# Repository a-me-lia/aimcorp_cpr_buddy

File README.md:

# Production Instructions

The files in the `/production` folder are ready for ordering at JLCPCB or most other PCB brokering services.

- **Board Design**: This board is designed as a 2-layer PCB. The quoting software should automatically select the minimum tolerances needed.
- **BOM Handling**: 
    - After uploading the BOM, if a component did not autopopulate, locate the corresponding designator in the BOM file.
    - Use the LCSC part number from the BOM to search in the JLC Parts library for an identical component.
    - LCSC "C-numbers" can be directly used in JLCPCB for part selection.

# Programming Instructions

This board is compatible with a standard 6-pin FTDI breakout for programming.

- **Programming Port**: The programming port is not populated with a pin header, allowing direct insertion of the FTDI board.
- **Bootloader Mode Strapping**: Refer to the [ESP-12F datasheet](https://www.espressif.com/sites/default/files/documentation/0a-esp8266ex_datasheet_en.pdf) for details on bootloader mode strapping.
    - All physical interfaces for pin strapping are accessible via a 4-pin interface on the board.

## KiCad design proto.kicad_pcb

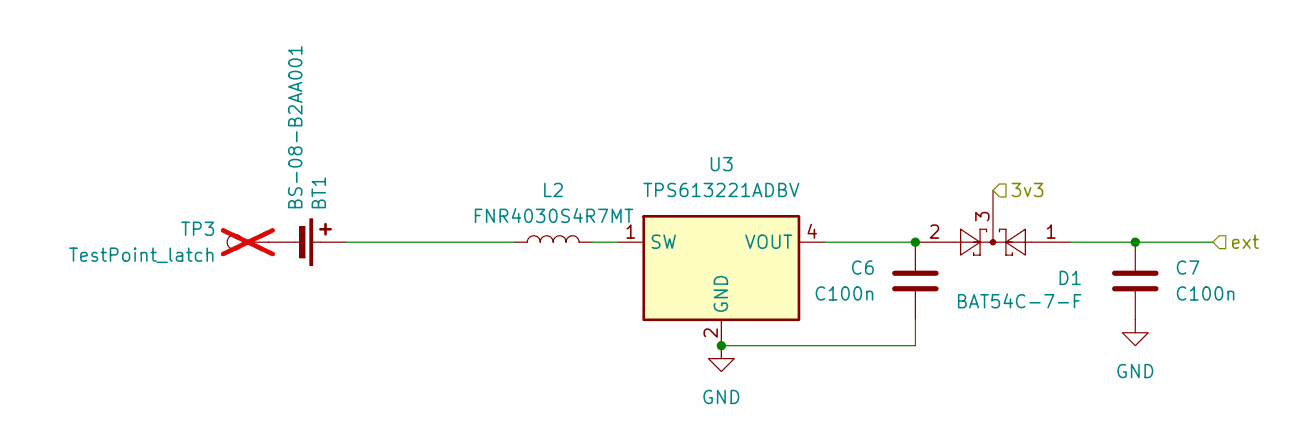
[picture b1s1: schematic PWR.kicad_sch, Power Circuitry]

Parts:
BT1: BS-08-B2AA001; LCSC C964777
C6, C7: C100n; C_0402_1005Metric; LCSC C60474
D1: BAT54C-7-F; SOT-23; LCSC C556168
L2: FNR4030S4R7MT; L_Changjiang_FNR4030S; LCSC C167874
TP3: TestPoint_latch; TestPoint_Bridge_Pitch2.0mm_Drill0.7mm; not fitted
U3: TPS613221ADBV; SOT-23-5; LCSC C2071121

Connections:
/DIFFAMP/3v3: D1.3; also elsewhere on the board
/ESP/ext: C7.1, D1.1; also elsewhere on the board
GND: C6.2, C7.2, U3.2 (GND); also elsewhere on the board
unnamed: BT1.+, L2.1
unnamed: BT1.-, TP3.1
unnamed: L2.2, U3.1 (SW)
unnamed: C6.1, D1.2, U3.4 (VOUT)

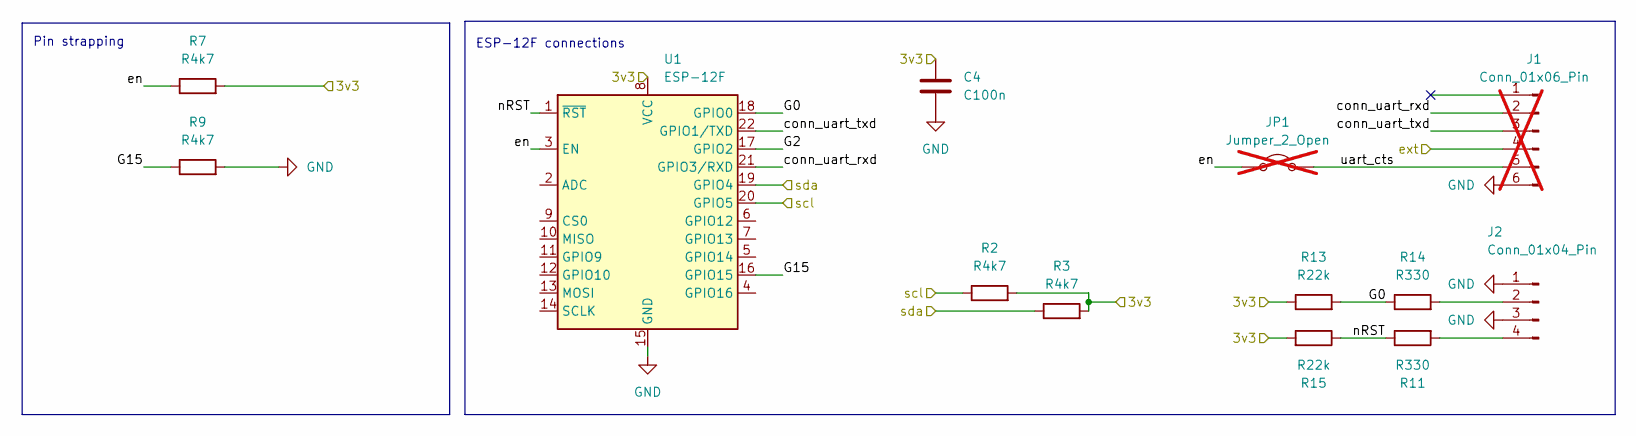
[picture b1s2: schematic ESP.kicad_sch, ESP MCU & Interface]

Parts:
C4: C100n; C_0402_1005Metric; LCSC C60474
J1: Conn_01x06_Pin; PinHeader_1x06_P2.54mm_Vertical; not fitted
J2: Conn_01x04_Pin; PinHeader_1x04_P2.54mm_Vertical; LCSC C6332197
JP1: Jumper_2_Open; SolderJumper-2_P1.3mm_Open_TrianglePad1.0x1.5mm; not fitted
R2, R3, R7, R9: R4k7; R_0402_1005Metric; LCSC C25940
R11, R14: R330; R_0402_1005Metric; LCSC C25104
R13, R15: R22k; R_0402_1005Metric; LCSC C82868
U1: ESP-12F; ESP-12E; LCSC C82891

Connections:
/DIFFAMP/3v3: C4.1, R2.2, R3.2, R7.2, R13.1, R15.2, U1.8 (VCC); also elsewhere on the board
/DIFFAMP/scl: R2.1, U1.20 (GPIO5); also elsewhere on the board
/DIFFAMP/sda: R3.1, U1.19 (GPIO4); also elsewhere on the board
/ESP/G0: R13.2, R14.1, U1.18 (GPIO0)
/ESP/G2: U1.17 (GPIO2)
/ESP/G15: R9.1, U1.16 (GPIO15)
/ESP/conn_uart_rxd: J1.2, U1.21 (GPIO3/RXD)
/ESP/conn_uart_txd: J1.3, U1.22 (GPIO1/TXD)
/ESP/en: JP1.1 (A), R7.1, U1.3 (EN)
/ESP/ext: J1.4; also elsewhere on the board
/ESP/nRST: R11.1, R15.1, U1.1 (~RST)
/ESP/uart_cts: J1.5, JP1.2 (B)
GND: C4.2, J1.6, J2.1, J2.3, R9.2, U1.15 (GND); also elsewhere on the board
unnamed: J2.2, R14.2
unnamed: J2.4, R11.2

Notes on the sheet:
Pin strapping
ESP-12F connections

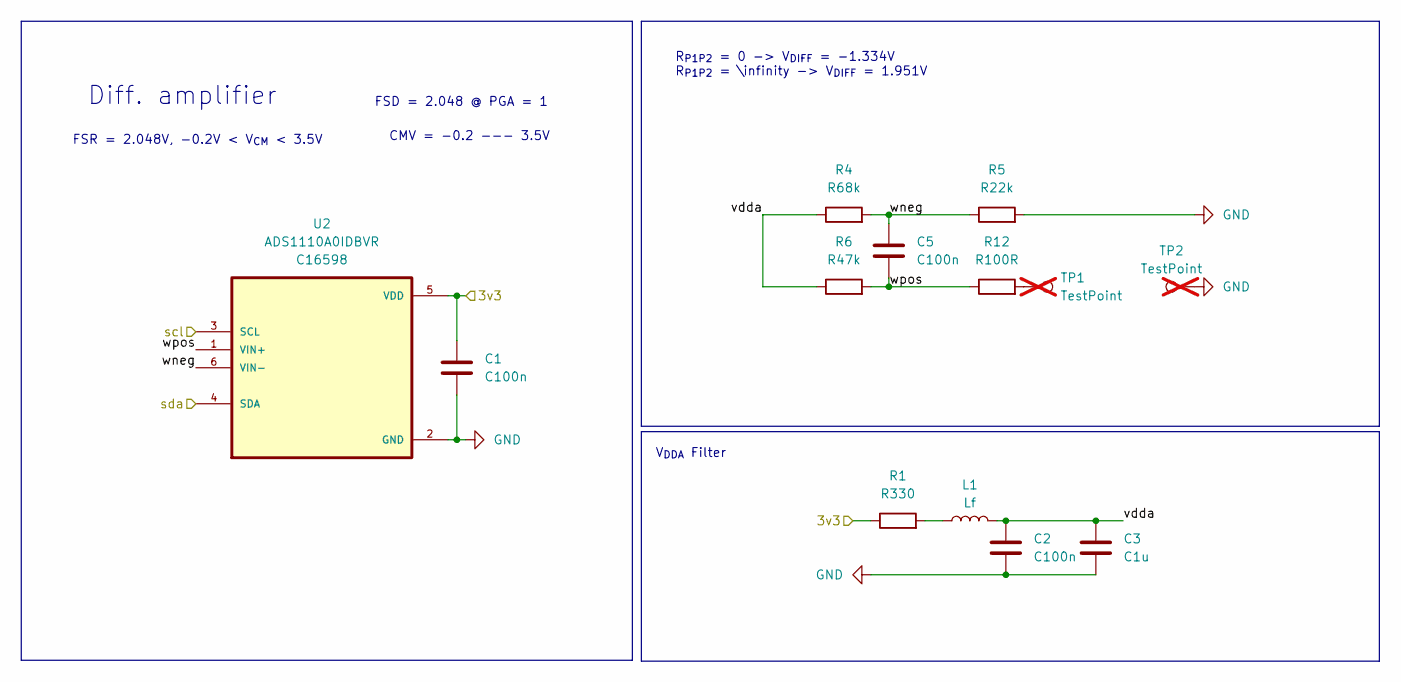
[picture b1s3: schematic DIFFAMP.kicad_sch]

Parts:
C1, C2, C5: C100n; C_0402_1005Metric; LCSC C60474
C3: C1u; C_0402_1005Metric; LCSC C14445
L1: Lf; L_0402_1005Metric; LCSC C2885921
R1: R330; R_0402_1005Metric; LCSC C25104
R4: R68k; R_0402_1005Metric; LCSC C36871
R5: R22k; R_0402_1005Metric; LCSC C82868
R6: R47k; R_0402_1005Metric; LCSC C93943
R12: R100R; R_0402_1005Metric; LCSC C106232
TP1, TP2: TestPoint; not fitted
U2: ADS1110A0IDBVR; SOT95P280X145-6N; LCSC C16598

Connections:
/DIFFAMP/3v3: C1.1, R1.1, U2.5 (VDD); also elsewhere on the board
/DIFFAMP/scl: U2.3 (SCL); also elsewhere on the board
/DIFFAMP/sda: U2.4 (SDA); also elsewhere on the board
/DIFFAMP/vdda: C2.1, C3.1, L1.2, R4.1, R6.1
/DIFFAMP/wneg: C5.1, R4.2, R5.1, U2.6 (VIN-)
/DIFFAMP/wpos: C5.2, R6.2, R12.1, U2.1 (VIN+)
GND: C1.2, C2.2, C3.2, R5.2, TP2.1, U2.2 (GND); also elsewhere on the board
unnamed: L1.1, R1.2
unnamed: R12.2, TP1.1

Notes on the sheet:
FSR = 2.048V, -0.2V < V_{CM} < 3.5V
V_{DDA} Filter
R_{P1P2} = 0 -> V_{DIFF} = -1.334V R_{P1P2} = \infinity -> V_{DIFF} = 1.951V
FSD = 2.048 @ PGA = 1
CMV = -0.2 --- 3.5V
Diff. amplifier

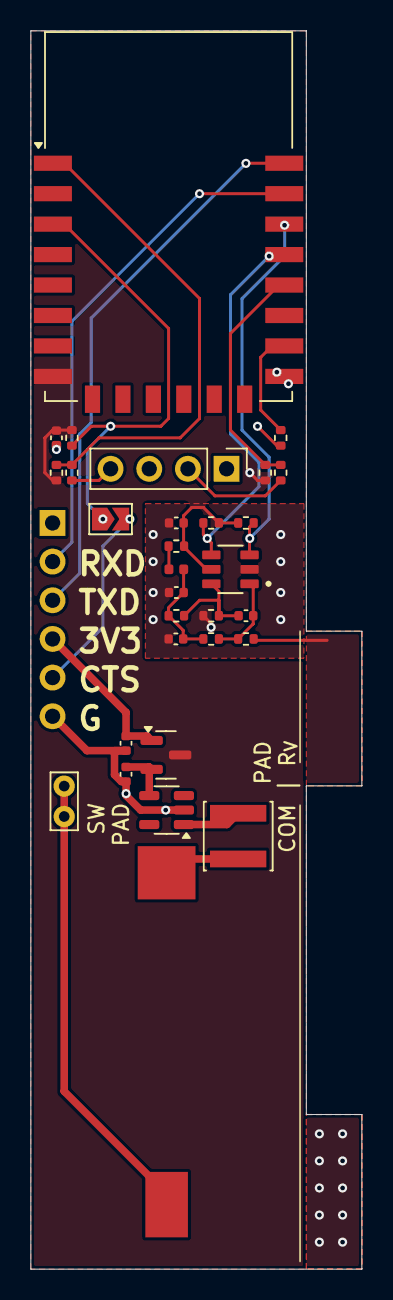
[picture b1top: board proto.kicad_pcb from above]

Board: 2 copper layers, 21.8 x 81.3 mm, 31 parts (0 on the bottom side), 22 nets.

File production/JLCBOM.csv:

Comment,Designator,Footprint,JLCPCB Part #,,
BS-08-B2AA001,BT1,BS-08-B2AA001,C964777,,
C100n,"C1,C2,C4,C5,C6,C7",Capacitor_SMD:C_0402_1005Metric,C60474,,
C1u,C3,Capacitor_SMD:C_0402_1005Metric, C14445,,
BAT54C-7-F,D1,Package_TO_SOT_SMD:SOT-23,C556168,,
Conn_01x04_Pin,J2,PinHeader_1x04_P2.54mm_Vertical,C6332197,,
Lf,L1,Inductor_SMD:L_0402_1005Metric,C2885921,,
FNR4030S4R7MT,L2,Inductor_SMD:L_Changjiang_FNR4030S,C167874,,
R330,"R1,R11,R14",Resistor_SMD:R_0402_1005Metric,C25104,,
R4k7,"R2,R3,R7,R9",Resistor_SMD:R_0402_1005Metric,C25940,,
R68k,R4,Resistor_SMD:R_0402_1005Metric,C36871,,
R22k,"R5,R13,R15",Resistor_SMD:R_0402_1005Metric,C82868,,
R47k,R6,Resistor_SMD:R_0402_1005Metric,C93943,,
R100R,R12,Resistor_SMD:R_0402_1005Metric,C106232,,
ESP-12F,U1,RF_Module:ESP-12E,C82891,,
ADS1110A0IDBVR,U2,SOT95P280X145-6N,C16598,,
TPS613221ADBV,U3,Package_TO_SOT_SMD:SOT-23-5,C2071121,,

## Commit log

2024-11-05 fix the README
2024-11-05 update the PDF
